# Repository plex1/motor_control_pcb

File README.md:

# Motor Control PCB 

Mainly an carrier for the follwing modules:
- 1x [A-Star 328PB Micro](https://www.pololu.com/category/239/a-star-328pb-micro) (compatible with Arduino)
  - 3.3 V, 12 MHz version (yellow power LED)
- 2x [DRV8834 Low-Voltage Stepper Motor Driver Carrier](https://www.pololu.com/product/2134)

## Libraries

Uses the following libraries:
- KiCad Symbol Library: [ioda_symbols](https://github.com/plex1/ioda_symbols)
- KiCad Footprint Library: [ioda_footprints](https://github.com/plex1/ioda_footprints)

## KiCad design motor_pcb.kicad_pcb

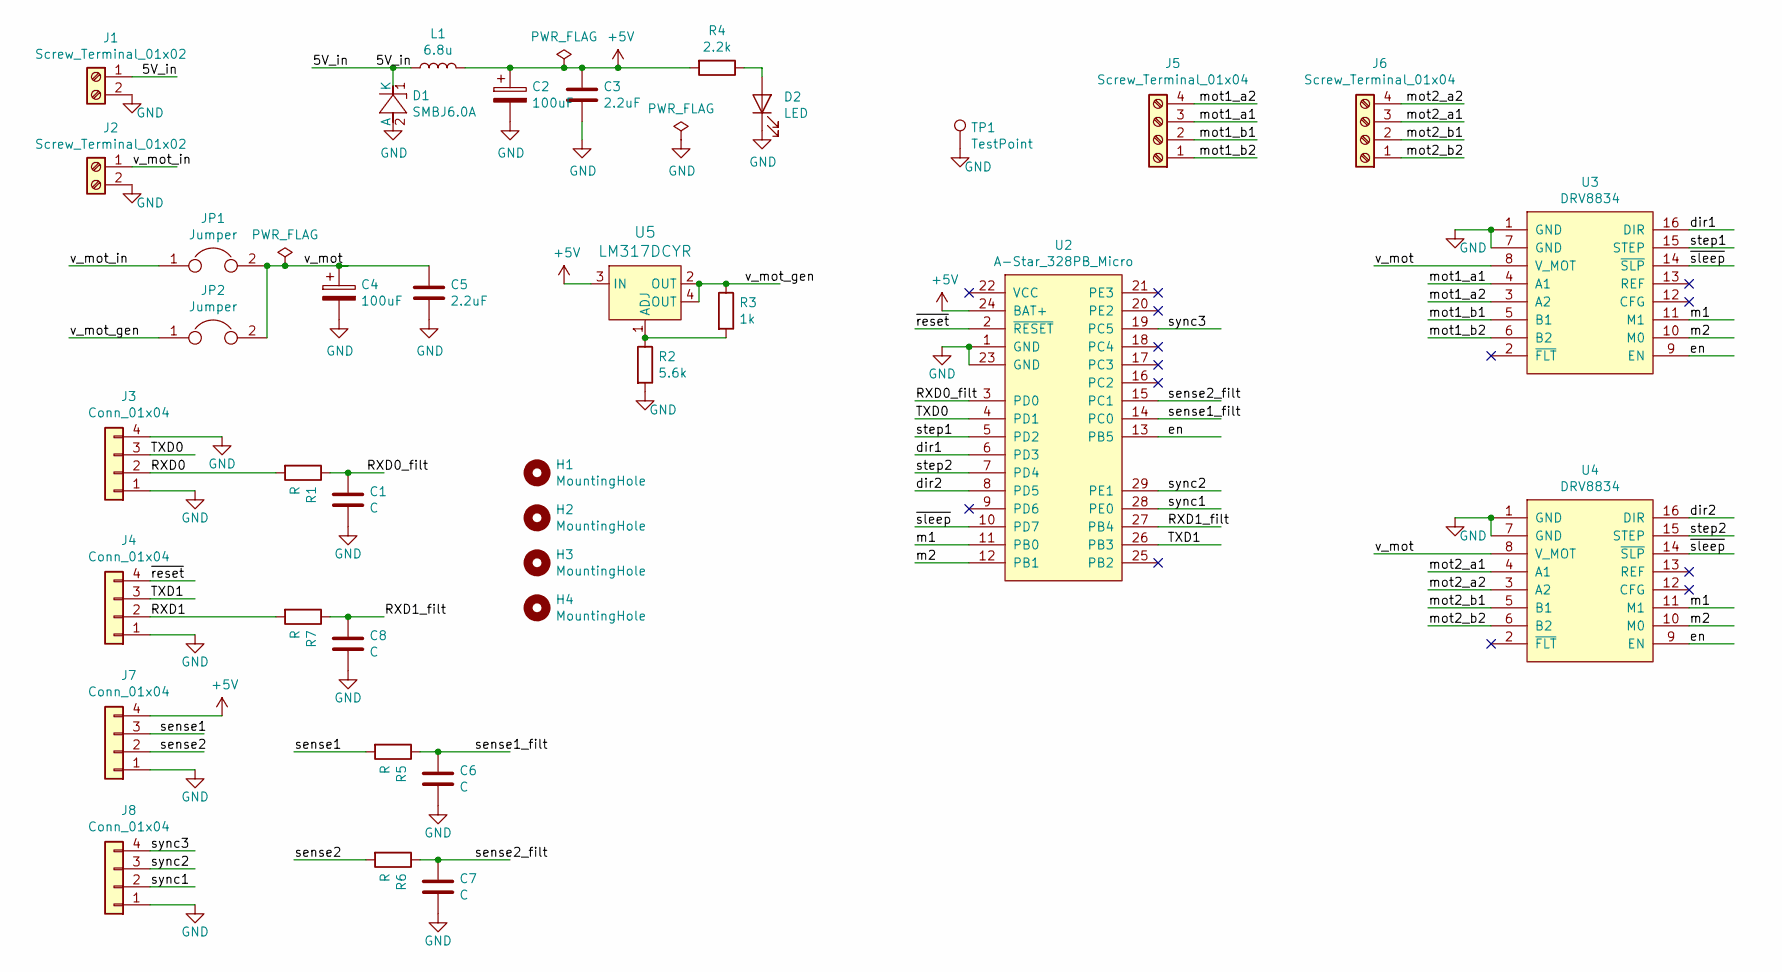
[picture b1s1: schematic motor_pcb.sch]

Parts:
C1, C6, C7, C8: C; C_0603_1608Metric
C2, C4: 100uF; CAPAE660X800N; Digi-Key_PN PCE5024CT-ND
C3, C5: 2.2uF; C_0603_1608Metric; Digi-Key_PN 490-12740-1-ND
D1: SMBJ6.0A; DO214AA_1(K)-2(A); Digi-Key_PN SMBJ6.0ABCT-ND
D2: LED; LED_0805; Digi-Key_PN 160-1423-1-ND
H1, H2, H3, H4: MountingHole; MountingHole_3.2mm_M3
J1, J2: Screw_Terminal_01x02; ScrewTerminal_1x02_P2.54mm_Vertical; Digi-Key_PN A98333-ND
J3, J4, J7, J8: Conn_01x04; Molex_PicoBlade_53261-0471_1x04-1MP_P1.25mm_Horizontal
J5, J6: Screw_Terminal_01x04; PinHeader_1x04_P2.54mm_Vertical
JP1, JP2: Jumper; R_0805_2012Metric
L1: 6.8u; INDP7373X46N; Digi-Key_PN 811-1180-1-ND
R1, R5, R6, R7: R; R_0603_1608Metric
R2: 5.6k; R_0603_1608Metric
R3: 1k; R_0603_1608Metric
R4: 2.2k; R_0603_1608Metric; Digi-Key_PN RMCF0603FT2K20CT-ND
TP1: TestPoint; PinHeader_1x01_P1.27mm_Vertical
U2: A-Star_328PB_Micro; DIP-24_600_ELL_15.24mm-spacing
U3, U4: DRV8834; DIP-16_500_ELL_12.7mm-spacing
U5: LM317DCYR; SOT-223-4; MPN LM317DCYR; Digi-Key_PN 296-12602-1-ND

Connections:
+5V: C2.1, C3.1, J7.4, L1.2, R4.2, U2.24 (BAT+), U5.3 (IN)
/5V_in: D1.1 (K), J1.1, L1.1
/RXD0: J3.2, R1.2
/RXD0_filt: C1.1, R1.1, U2.3 (PD0)
/RXD1: J4.2, R7.2
/RXD1_filt: C8.1, R7.1, U2.27 (PB4)
/TXD0: J3.3, U2.4 (PD1)
/TXD1: J4.3, U2.26 (PB3)
/dir1: U2.6 (PD3), U3.16 (DIR)
/dir2: U2.8 (PD5), U4.16 (DIR)
/en: U2.13 (PB5), U3.9 (EN), U4.9 (EN)
/m1: U2.11 (PB0), U3.11 (M1), U4.11 (M1)
/m2: U2.12 (PB1), U3.10 (M0), U4.10 (M0)
/mot1_a1: J5.3, U3.4 (A1)
/mot1_a2: J5.4, U3.3 (A2)
/mot1_b1: J5.2, U3.5 (B1)
/mot1_b2: J5.1, U3.6 (B2)
/mot2_a1: J6.3, U4.4 (A1)
/mot2_a2: J6.4, U4.3 (A2)
/mot2_b1: J6.2, U4.5 (B1)
/mot2_b2: J6.1, U4.6 (B2)
/sense1: J7.3, R5.2
/sense1_filt: C6.1, R5.1, U2.14 (PC0)
/sense2: J7.2, R6.2
/sense2_filt: C7.1, R6.1, U2.15 (PC1)
/step1: U2.5 (PD2), U3.15 (STEP)
/step2: U2.7 (PD4), U4.15 (STEP)
/sync1: J8.2, U2.28 (PE0)
/sync2: J8.3, U2.29 (PE1)
/sync3: J8.4, U2.19 (PC5)
/v_mot: C4.1, C5.1, JP1.2, JP2.2, U3.8 (V_MOT), U4.8 (V_MOT)
/v_mot_gen: JP2.1, R3.1, U5.2 (OUT), U5.4 (OUT)
/v_mot_in: J2.1, JP1.1
/~reset: J4.4, U2.2 (~RESET)
/~sleep: U2.10 (PD7), U3.14 (~SLP), U4.14 (~SLP)
GND: C1.2, C2.2, C3.2, C4.2, C5.2, C6.2, C7.2, C8.2, D1.2 (A), D2.1 (K), J1.2, J2.2, J3.1, J3.4, J4.1, J7.1, J8.1, R2.2, TP1.1, U2.1 (GND), U2.23 (GND), U3.1 (GND), U3.7 (GND), U4.1 (GND), U4.7 (GND)
unnamed: D2.2 (A), R4.1
unnamed: R2.1, R3.2, U5.1 (ADJ)

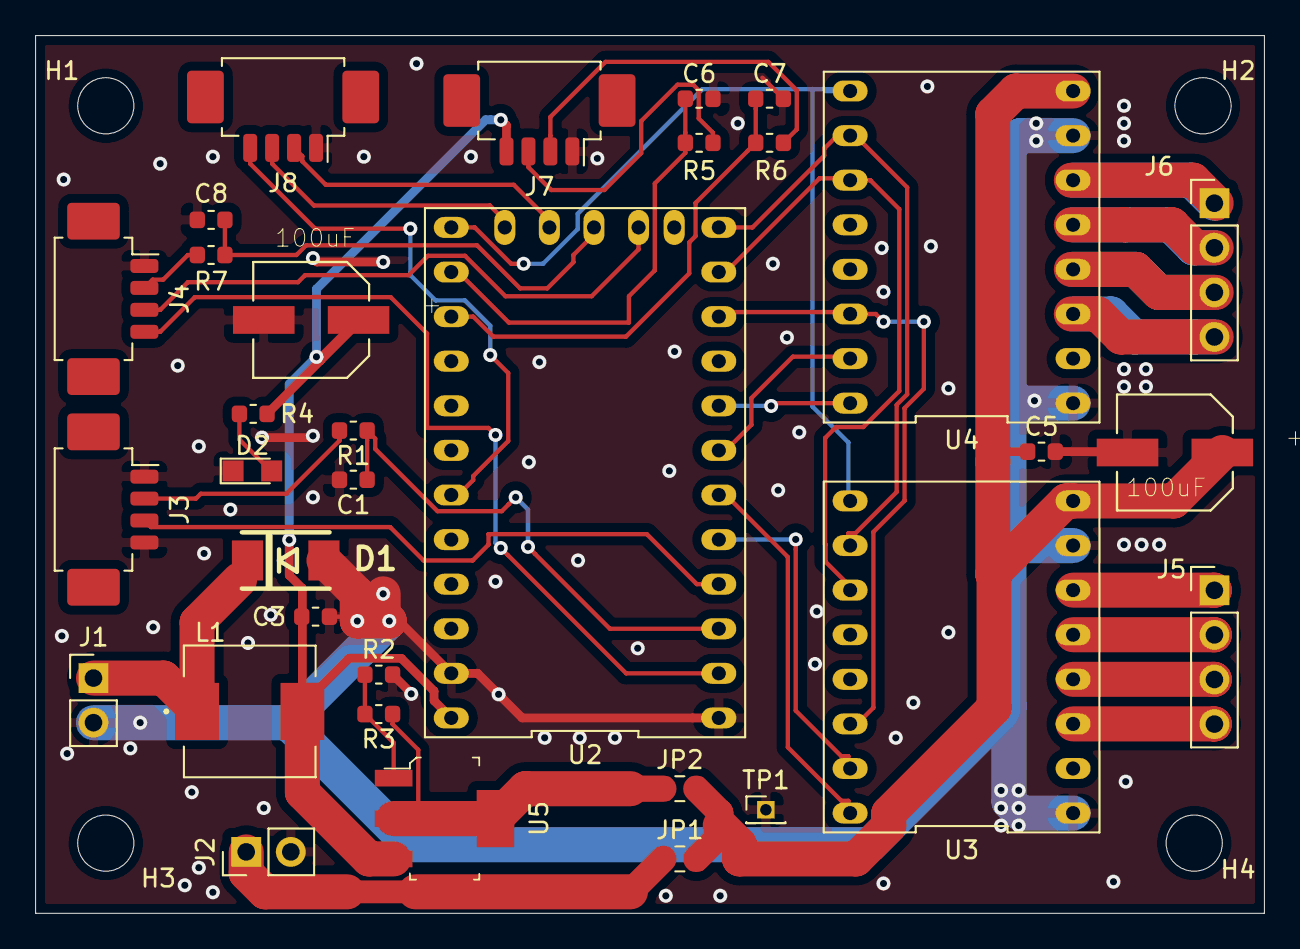
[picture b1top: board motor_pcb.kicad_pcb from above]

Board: 2 copper layers, 70.0 x 50.0 mm, 37 parts (0 on the bottom side), 38 nets.

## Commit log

2019-11-19 Initial version
2019-11-19 added 5V to sensor connector
2024-08-07 updated with previously uncommitted changes. Added schematics
